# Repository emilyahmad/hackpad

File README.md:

cool, waiting on pcb to arrive

[bom](bom.csv)

Redesigning this to be s'mores themed

new schem

pcb wired

# Macropad ᶻ 𝗓 𐰁 .ᐟ

A simple macropad with an OLED screen, 1 LED and 6 switches. Have a few different ideas on how I'll use it/firmware, some ideas: keyboard shortcuts for git commands, game controller, MIDI controller. Made using @Alex Ren's hackpad guide and Joe Scotto's keyboard guides.

# Photos

| Schematic                           | PCB                     | 3D Viewer             |
| ----------------------------------- | ----------------------- | --------------------- |
|  |  |  |

# BOM (Components)

| Item                   | Purpose           | Quantity   | Cost   | Source                                                                |
| ---------------------- | ----------------- | ---------- | ------ | --------------------------------------------------------------------- |
| D1                     | RGB LED           | 1 (MOQ 5)  | $0.43  | [LCSC C5149201](https://www.lcsc.com/product-detail/C5149201.html)    |
| D2, D3, D4, D5, D6, D7 | Signal Diode      | 6 (MOQ 50) | $1.09  | [LCSC C258182](https://www.lcsc.com/product-detail/C258182.html)      |
| J1                     | OLED 128x32       | 1          | $2.24  | [LCSC C5248081](https://www.lcsc.com/product-detail/C5248081.html)    |
| U1                     | Seeed XIAO RP2040 | 1          | $10.99 | [Amazon](https://www.amazon.com/gp/product/B0DRNSV5CS) (pre-soldered) |

# Assembly BOM

| Item                            | Purpose                             | Quantity   | Cost             | Source                                                                                                |
| ------------------------------- | ----------------------------------- | ---------- | ---------------- | ----------------------------------------------------------------------------------------------------- |
| PCB                             | functionality through MCU, mounting | 5          | $2, total $21.60 | JLCPCB                                                                                                |
| XDA keycaps (black transparent) | cover switches                      | 20         | $11.99           | [Amazon](https://www.amazon.com/gp/product/B0CQ2YM5FM/ref=ox_sc_act_image_1?smid=A1T1IN9BGLZH2U&th=1) |
| Solder Tip Cleaner              | clean flux                          | 1          | $9.99            | [Amazon](https://www.amazon.com/gp/product/B0CNVS7BFZ/ref=ox_sc_act_image_3?smid=A328EBN1BG6NU5&th=1) |
| Solder Wire                     | to solder                           | 1          | $9.99            | [Amazon](https://www.amazon.com/gp/product/B0B6397413/ref=ox_sc_act_image_4?smid=A2T4V9F5BIUYS6&th=1) |
| Mini Soldering Iron             | to solder                           | 1          | $39.99           | [Amazon](https://www.amazon.com/gp/product/B096X6SG13/ref=ox_sc_act_image_5?smid=AS24VHUSR1W5D&psc=1) |
| S1, S2, S3, S4, S5, S6          | MX switches, brown                  | 6 (MOQ 20) | $8.99            | [Amazon](https://www.amazon.com/gp/product/B0888JHM58/ref=ox_sc_act_image_6?smid=A2U3R73MNHPWPS&th=1) |

Macropad Total: $57.33
with Soldering kit: $117.30

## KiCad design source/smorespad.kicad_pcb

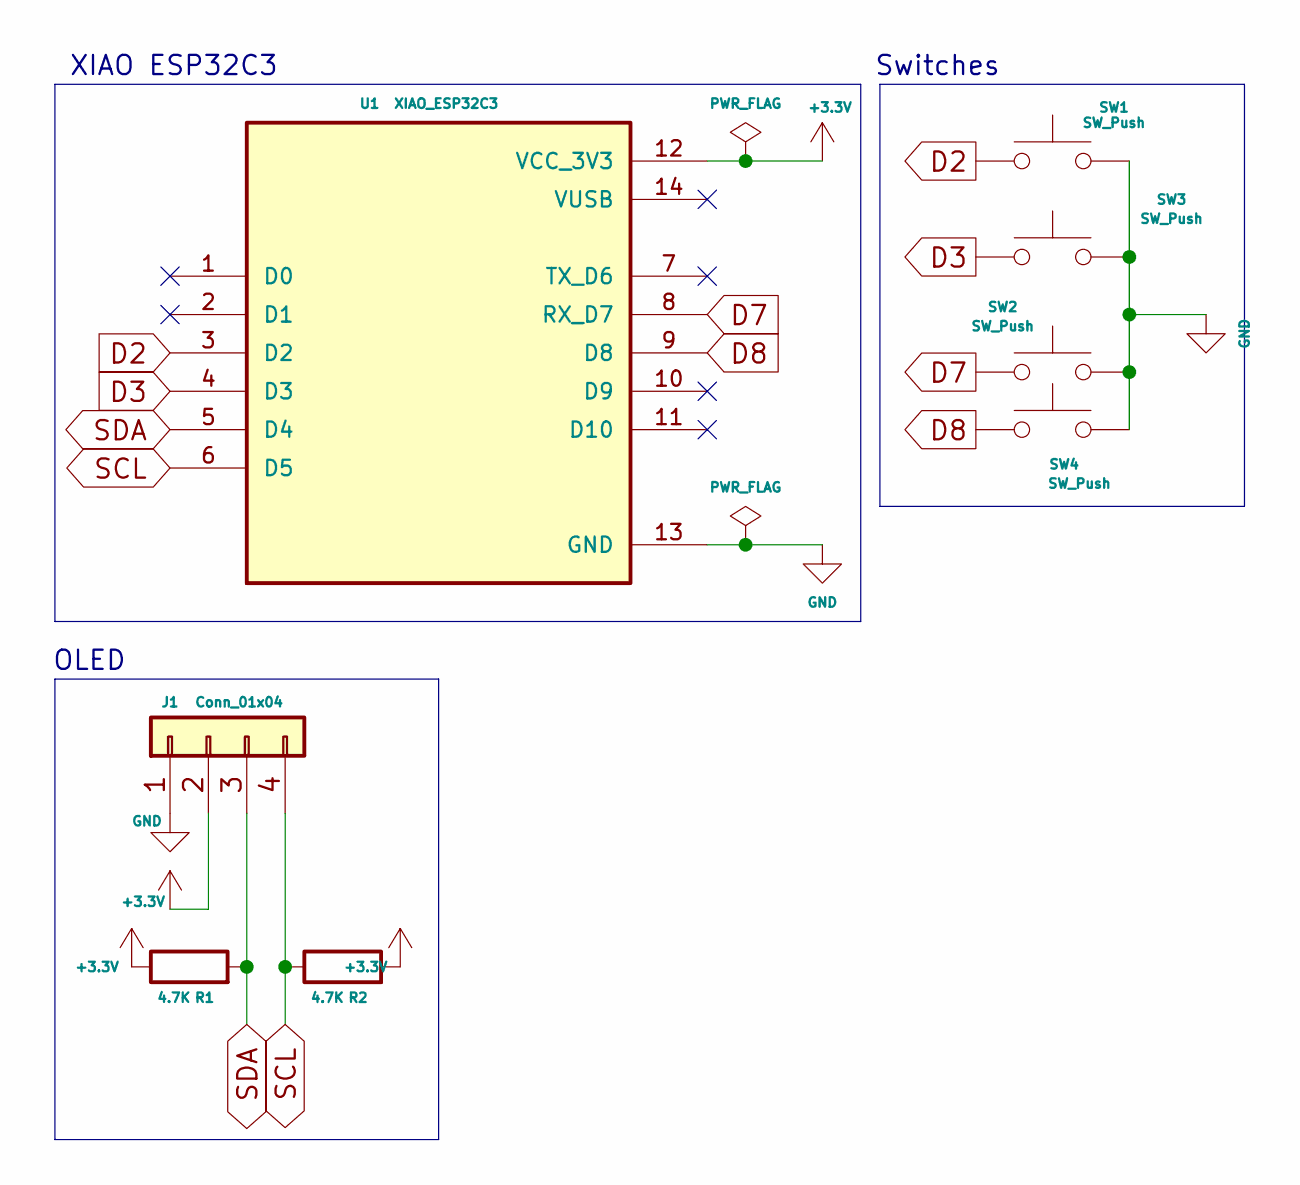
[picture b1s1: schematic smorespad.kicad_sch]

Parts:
J1: Conn_01x04; PinSocket_1x04_P2.54mm_Vertical
R1, R2: 4.7K; R_Axial_DIN0207_L6.3mm_D2.5mm_P7.62mm_Horizontal
SW1, SW2, SW3, SW4: SW_Push; SW_Cherry_MX_1.00u_PCB
U1: XIAO_ESP32C3; MODULE_XIAO_ESP32C3; PARTREV 23/05/2022

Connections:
+3.3V: J1.2, R1.1, R2.2, U1.12 (VCC_3V3)
D2: SW1.1, U1.3 (D2)
D3: SW3.1, U1.4 (D3)
D7: SW2.1, U1.8 (RX_D7)
D8: SW4.1, U1.9 (D8)
GND: J1.1, SW1.2, SW2.2, SW3.2, SW4.2, U1.13 (GND)
SCL: J1.4, R2.1, U1.6 (D5)
SDA: J1.3, R1.2, U1.5 (D4)

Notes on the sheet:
OLED
Switches
XIAO ESP32C3

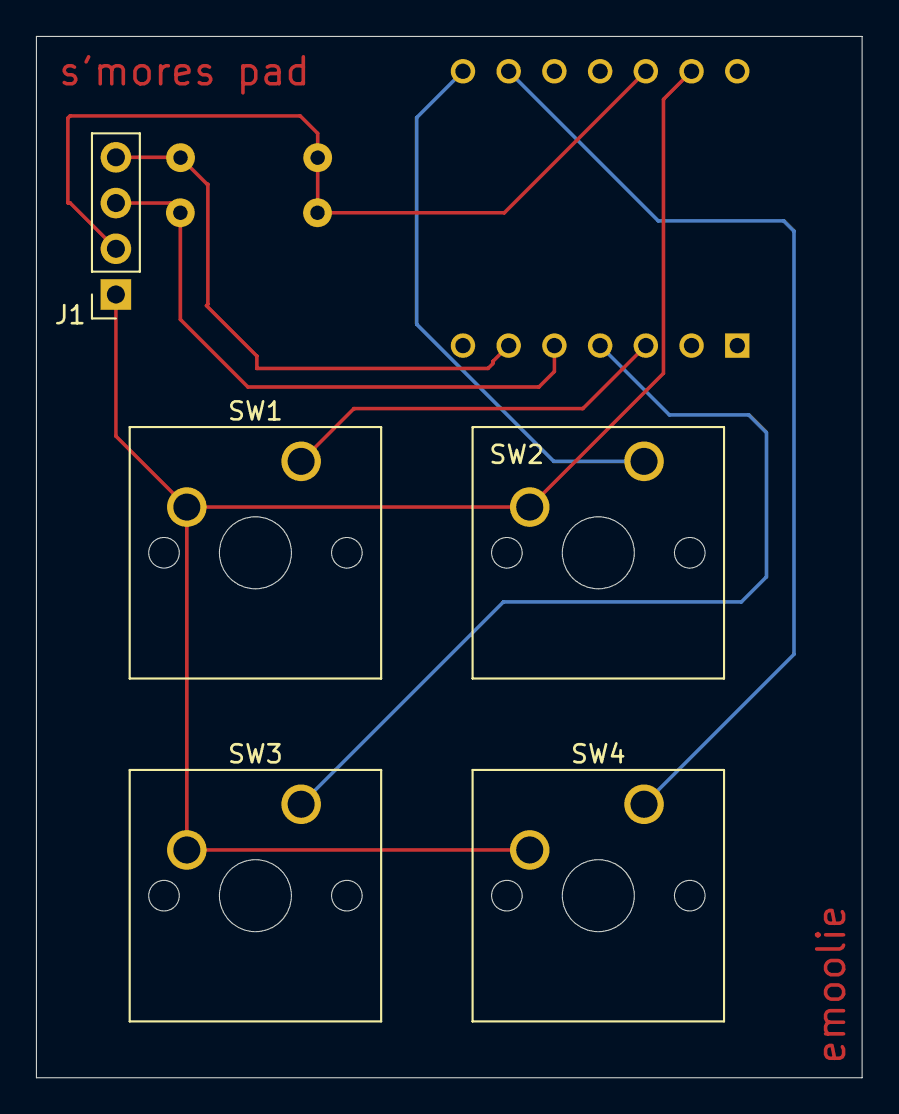
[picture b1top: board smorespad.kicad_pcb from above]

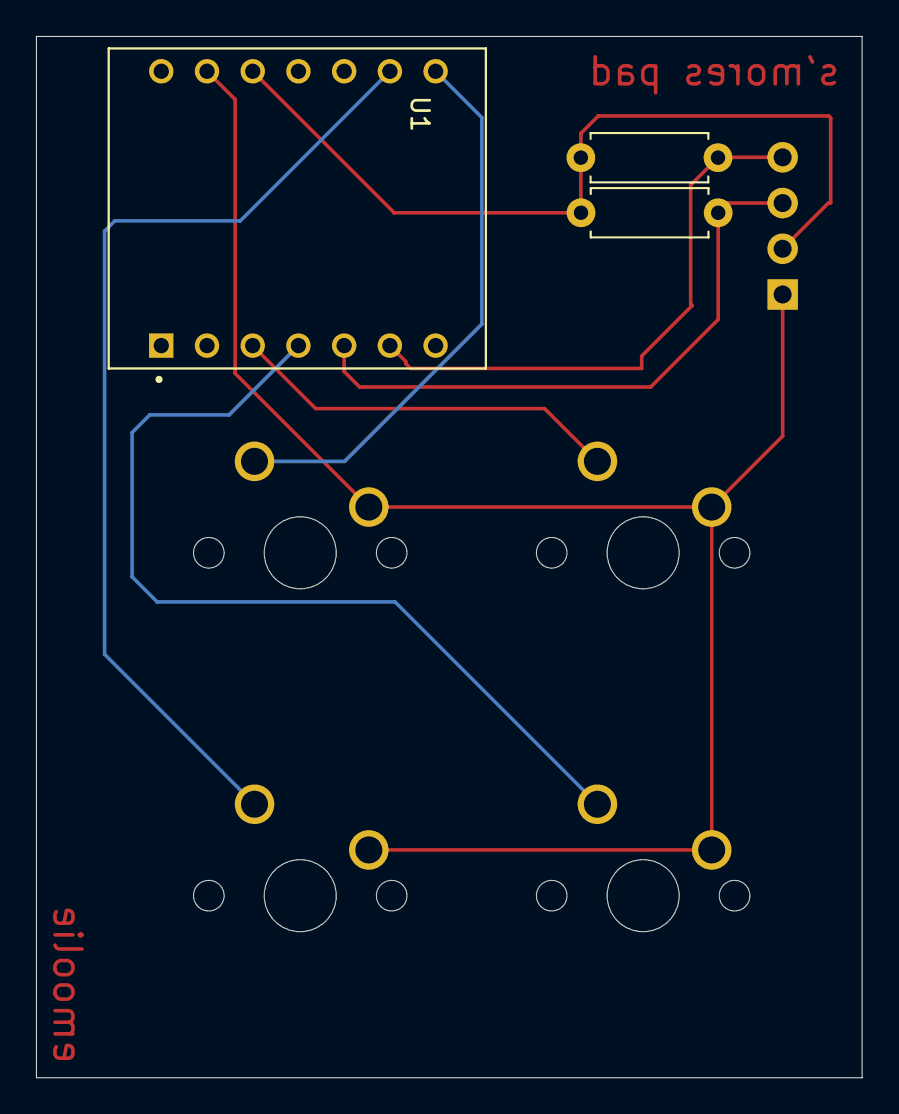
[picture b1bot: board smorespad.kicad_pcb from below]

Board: 2 copper layers, 45.9 x 57.9 mm, 8 parts (3 on the bottom side), 8 nets.

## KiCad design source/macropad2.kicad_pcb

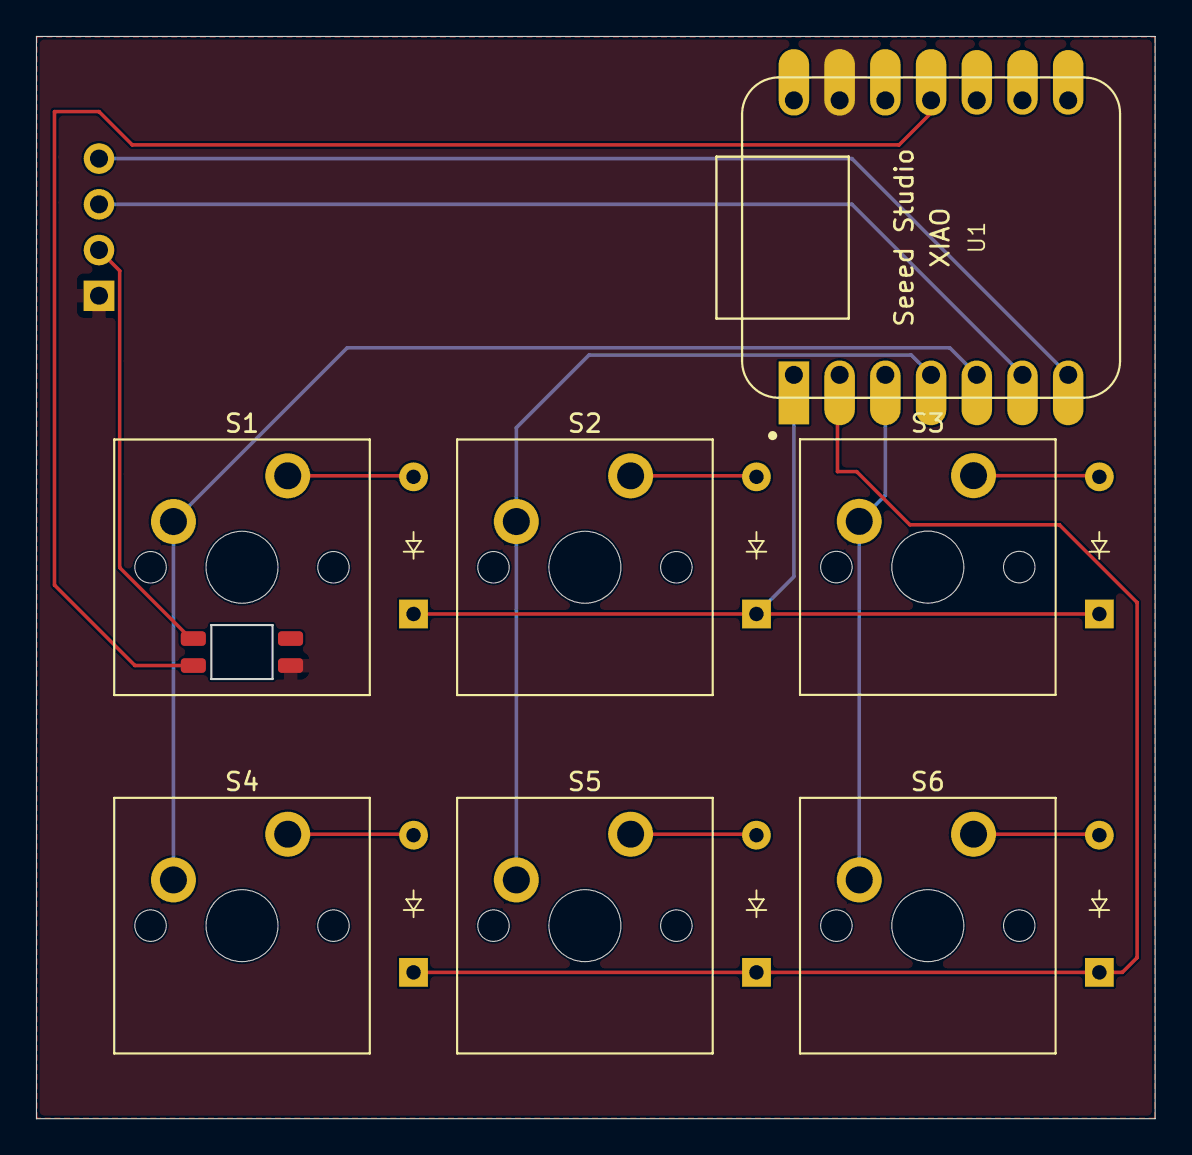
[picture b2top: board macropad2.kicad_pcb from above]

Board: 2 copper layers, 62.1 x 60.1 mm, 15 parts (0 on the bottom side), 16 nets.

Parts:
D1: LED_SK6812MINI
D2, D3, D4, D5, D6, D7: Diode_DO-35
J1: OLED_128x32
S1, S2, S3, S4, S5, S6: MX_PCB_1.00u
U1: MOUDLE-SEEEDUINO-XIAO; XIAO-Generic-Hybrid-14P-2.54-21X17.8MM

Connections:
+5V: D1.4 (DIN), J1.2 (VCC)
Col 0: S1.1, S4.1, U1.5 (PA8_A4_D4_SDA)
Col 1: S2.1, S5.1, U1.4 (PA11_A3_D3)
Col 2: S3.1, S6.1, U1.3 (PA10_A2_D2)
GND: D1.2 (DOUT), J1.1 (GND), U1.13 (GND)
LED: D1.3 (VSS), U1.11 (PA6_A10_D10_MOSI)
unnamed: D2.2 (A), S1.2
unnamed: D3.2 (A), S2.2
unnamed: D4.2 (A), S3.2
unnamed: D5.2 (A), S4.2
unnamed: D6.2 (A), S5.2
unnamed: D7.2 (A), S6.2
Row 0: D2.1 (K), D3.1 (K), D4.1 (K), U1.1 (PA02_A0_D0)
Row 1: D5.1 (K), D6.1 (K), D7.1 (K), U1.2 (PA4_A1_D1)
SCL: J1.3 (SCL), U1.6 (PA9_A5_D5_SCL)
SDA: J1.4 (SDA), U1.7 (PB08_A6_D6_TX)

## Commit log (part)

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2026-05-05 updated files
2026-05-06 updated BOM
2026-05-06 fixed table & image paths
2026-05-06 table fix
2026-05-06 added kicad files
